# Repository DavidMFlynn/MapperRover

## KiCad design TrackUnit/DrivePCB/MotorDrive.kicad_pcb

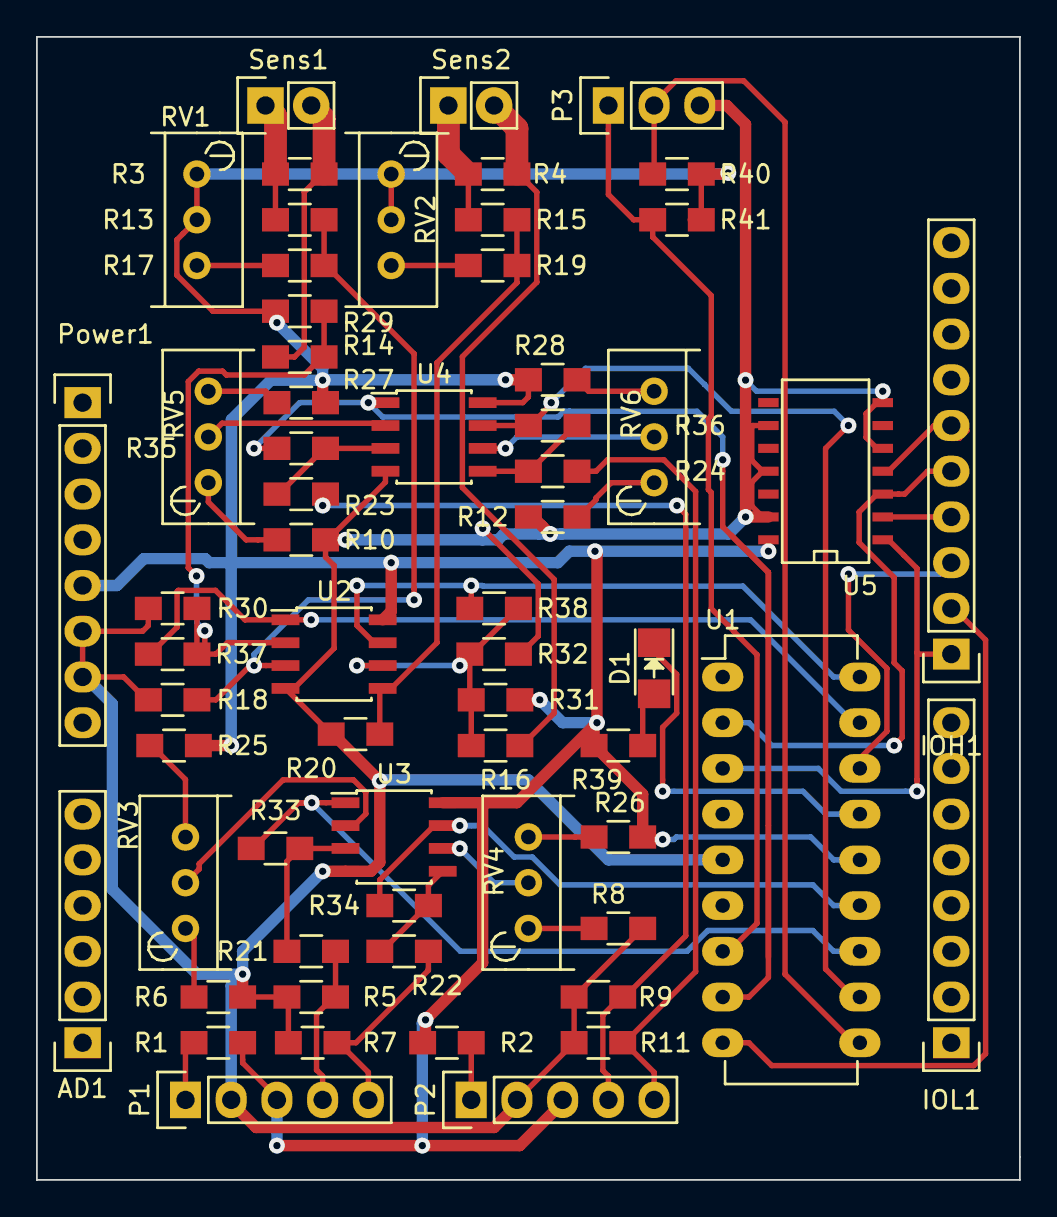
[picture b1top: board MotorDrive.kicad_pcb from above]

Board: 2 copper layers, 54.6 x 63.5 mm, 62 parts (0 on the bottom side), 50 nets.

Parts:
AD1: CONN_01X06; Pin_Header_Straight_1x06
D1: LED; LED-1206
IOH1: CONN_01X10; Pin_Header_Straight_1x10
IOL1: CONN_01X08; Pin_Header_Straight_1x08
P1, P2: CONN_01X05; Pin_Header_Straight_1x05
P3: CONN_01X03; Pin_Header_Straight_1x03
Power1: CONN_01X08; Pin_Header_Straight_1x08
R1, R2, R3, R4, R5, R6, R7, R8, R9, R10, R11, R12, R13, R14, R15, R16, R17, R18, R19, R20, R21, R22, R23, R24, R25, R26, R27, R28, R29, R30, R31, R32, R33, R34, R35, R36, R37, R38, R39, R40, R41: R; R_0805_HandSoldering
RV1, RV2, RV3, RV4, RV5, RV6: POT; Potentiometer_Bourns_3296W_3-8Zoll_Inline_ScrewUp
Sens1, Sens2: CONN_01X02; Pin_Header_Straight_1x02
U1: PIC16(L)F1847-I/P; DIP-18_W7.62mm_LongPads
U2, U3, U4: LM358; SOIC-8_3.9x4.9mm_Pitch1.27mm
U5: 74HC04; SOIC-14_N

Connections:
+5V: P1.3, P2.3, Power1.5, R1.1, R2.1, R25.2, R26.2, R27.2, R28.2, R29.2, R31.2, R39.1, R40.1, R41.1, RV1.1, RV1.2, RV2.1, RV2.2, U1.14, U2.8, U3.8, U4.8, U5.14
GND: P1.2, P2.2, P3.3, Power1.6, Power1.7, R5.1, R6.2, R7.1, R8.2, R9.1, R10.2, R11.1, R12.2, R18.1, R20.1, R30.1, R32.1, U1.5, U2.4, U3.4, U4.4, U5.5, U5.7, U5.9, U5.11, U5.13
unnamed: D1.1, U1.15
unnamed: D1.2, R39.2
unnamed: IOH1.1, U1.3, U5.1
unnamed: IOH1.2, U1.9
unnamed: IOH1.3, U1.16
unnamed: IOH1.4, U5.2
unnamed: IOH1.5, U1.2, U5.3
unnamed: IOH1.6, U5.4
unnamed: P1.1, R1.2
unnamed: P1.4, R5.2, R21.2
unnamed: P1.5, R7.2, R22.2
unnamed: P2.1, R2.2
unnamed: P2.4, R9.2, R23.2
unnamed: P2.5, R11.2, R24.2
unnamed: P3.1, R41.2, U1.7
unnamed: P3.2, R40.2, U1.10
unnamed: R6.1, RV3.1
unnamed: R8.1, RV4.1
unnamed: R10.1, RV5.1
unnamed: R12.1, RV6.1
unnamed: R13.1, R17.1, R18.2, U2.3
unnamed: R3.2, R13.2, Sens1.1
unnamed: R14.1, R29.1, R30.2, R37.2, U2.2
unnamed: R3.1, R14.2, Sens1.2
unnamed: R15.1, R19.1, R20.2, U2.5
unnamed: R4.2, R15.2, Sens2.1
unnamed: R16.1, R31.1, R32.2, R38.2, U2.6
unnamed: R4.1, R16.2, Sens2.2
unnamed: R17.2, RV1.3
unnamed: R19.2, RV2.3
unnamed: R21.1, R33.2, U3.3
unnamed: R22.1, R34.2, U3.5
unnamed: R23.1, R35.2, U4.3
unnamed: R24.1, R36.2, U4.5
unnamed: R25.1, RV3.3
unnamed: R26.1, RV4.3
unnamed: R27.1, RV5.3
unnamed: R28.1, RV6.3
unnamed: R33.1, U1.12, U3.1
unnamed: R34.1, U1.13, U3.7
unnamed: R35.1, U1.8, U4.1
unnamed: R36.1, U1.11, U4.7
unnamed: R37.1, U1.17, U2.1
unnamed: R38.1, U1.18, U2.7
unnamed: RV3.2, U3.2
unnamed: RV4.2, U3.6
unnamed: RV5.2, U4.2
unnamed: RV6.2, U4.6

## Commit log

2017-04-08 new repo
2017-04-09 minor fix
2017-04-12 Firmware 1.0d2
    Getting organized.
2017-04-12 PWM init
2017-04-12 MotorTest
2017-04-13 TMR2IE
2017-04-13 Motor test is go
2017-04-14 Added I2C stuff
2017-04-18 PID started
2017-04-20 CalcSpeed
2017-04-20 A test of GIT
2017-04-21 with gain
2017-04-21 and again
2017-04-21 Running at speed
    A good speed test spd=5 gain=4
2017-04-21 cmd spd update
2017-04-23 CalcPosErr
2017-04-27 Test Ready
2017-10-04 pcb top pdf

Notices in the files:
TrackUnit/DrivePCB/MotorDrive.kicad_pcb:
DMFE 2016 GPL v2.0
